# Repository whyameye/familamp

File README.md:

# familamp
An IoT lamp based on John Harrison's Filimin networked RGB lights.

In essence, an inter-networked series of lamps using FastLED, ESP8266 and Arduino that 'communicate' by syncing across the internet.

I intend taking some elements from Horacio Bouzas' Web-configurable Wifi code for ESP8266, from 'Cheerlights' and from the amazing work done by the principals and contributors at FastLED.

John Harrrison's Filimin: 
https://www.hackster.io/filimin/networked-rgb-wi-fi-decorative-touch-lights

FastLED Google Plus Community: 
https://plus.google.com/u/0/communities/109127054924227823508

Horacio Bouzas' web code: 
http://horaciobouzas.com/2014/12/19/esp8266-based-web-configurable-wifi-general-purpose-control/

Hardware:

ESP8266 ESP-01 or ESP-03
Arduino Nano

Alternatively, Roman's wonderful Arduino PRO-compatible 'Wireless Sensor Board' would make a perfect platform:
https://www.tindie.com/products/ceech/wireless-sensor-board-w-atmega328p/

WS2811/WS2812 Addressable RGB LEDs - in either a strip or a ring (like Adafruit's NeoPixel ring)

With great thanks to John Harrison for the inspiration and encouragement.

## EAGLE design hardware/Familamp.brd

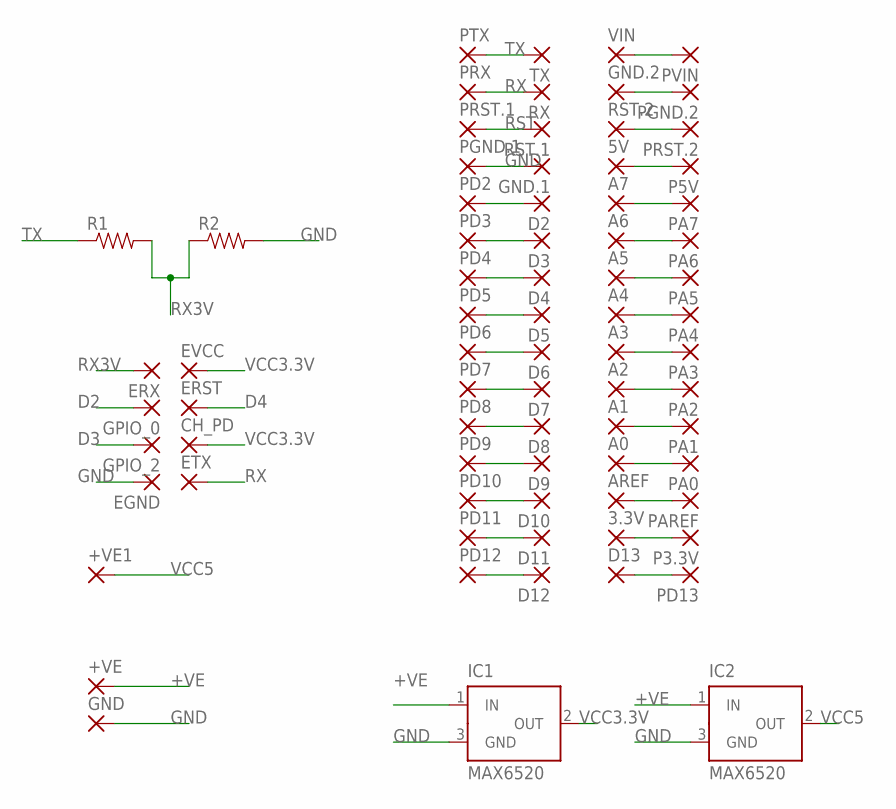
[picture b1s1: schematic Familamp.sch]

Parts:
3.3V, 5V: 1,6/0,9
+VE, +VE1: 2,15/1,0
A0, A1, A2, A3, A4, A5, A6, A7: 1,6/0,9
AREF: 1,6/0,9
CH_PD: 2,15/1,0
D2, D3, D4, D5, D6, D7, D8, D9, D10, D11, D12, D13: 1,6/0,9
EGND: 2,15/1,0
ERST: 2,15/1,0
ERX: 2,15/1,0
ETX: 2,15/1,0
EVCC: 2,15/1,0
GND: 2,15/1,0
GND.1, GND.2: 1,6/0,9
GPIO_0, GPIO_2: 2,15/1,0
IC1, IC2: MAX6520; SOT23
P3.3V, P5V: 1,6/0,9
PA0, PA1, PA2, PA3, PA4, PA5, PA6, PA7: 1,6/0,9
PAREF: 1,6/0,9
PD2, PD3, PD4, PD5, PD6, PD7, PD8, PD9, PD10, PD11, PD12, PD13: 1,6/0,9
PGND.1, PGND.2: 1,6/0,9
PRST.1, PRST.2: 1,6/0,9
PRX: 1,6/0,9
PTX: 1,6/0,9
PVIN: 1,6/0,9
R1, R2: RESISTORPTH-1/2W; AXIAL-0.5
RST.1, RST.2: 1,6/0,9
RX: 1,6/0,9
TX: 1,6/0,9
VIN: 1,6/0,9

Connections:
3.3V: AREF.1, PAREF.1
+VE: +VE.1, IC1.1 (IN), IC2.1 (IN), PVIN.1, VIN.1
A0: A0.1, PA0.1
A1: A1.1, PA1.1
A2: A2.1, PA2.1
A3: A3.1, PA3.1
A4: A4.1, PA4.1
A5: A5.1, PA5.1
A6: A6.1, PA6.1
A7: A7.1, PA7.1
AREF: 3.3V.1, P3.3V.1
D2: D2.1, GPIO_0.1, PD2.1
D3: D3.1, GPIO_2.1, PD3.1
D4: D4.1, ERST.1, PD4.1
D5: D5.1, PD5.1
D6: D6.1, PD6.1
D7: D7.1, PD7.1
D8: D8.1, PD8.1
D9: D9.1, PD9.1
D10: D10.1, PD10.1
D11: D11.1, PD11.1
D12: D12.1, PD12.1
D13: D13.1, PD13.1
GND: EGND.1, GND.1, GND.1.1, GND.2.1, IC1.3 (GND), IC2.3 (GND), PGND.1.1, PGND.2.1, R2.P$2 (2)
unnamed: 5V.1, P5V.1
RST: PRST.1.1, RST.1.1
RST.2: PRST.2.1, RST.2.1
RX: ETX.1, PRX.1, RX.1
RX3V: ERX.1, R1.P$2 (2), R2.P$1 (1)
TX: PTX.1, R1.P$1 (1), TX.1
VCC3.3V: CH_PD.1, EVCC.1, IC1.2 (OUT)
VCC5: +VE1.1, IC2.2 (OUT)

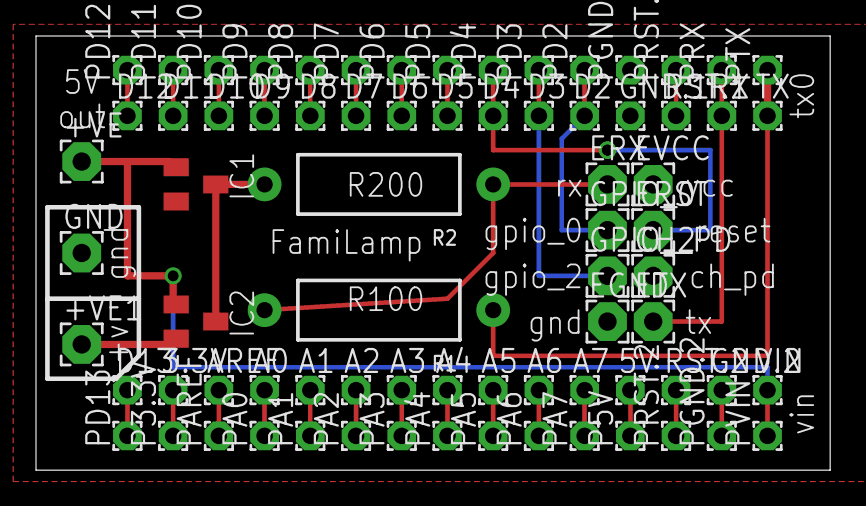
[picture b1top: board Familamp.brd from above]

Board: 2 copper layers, 44.1 x 24.1 mm, 75 parts (0 on the bottom side), 32 nets.

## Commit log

2015-05-23 Eagle files
    Created familamp.brd and familamp.sch eagle CAD files
2015-05-23 Updated webiot.lua
    Updated to include Horacio’s wifi code
2015-05-23 moved to led code directory
    To comply with Arduino IDE moved to led code directory and updated with
    initial FastLED sketch.
2015-05-23 Changed FastLED params
2015-05-23 Updated hardware
2015-05-23 spelling

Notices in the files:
parts and their libraries:
SparkFun-Passives: Licensing: Creative Commons ShareAlike 4.0 International - https://creativecommons.org/licenses/by-sa/4.0
